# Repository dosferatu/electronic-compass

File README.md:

Electronic-Compass
==================

An electronic compass using an ATMega32U4 microcontroller interfaced to an LSM303DLH accel/magnetomer IC and a Nokia 5110 LCD display.
The sensor is driven through the TWI bus, and the LCD is driven through the SPI bus.

Layout of the PCB is done in Eagle, and the software targets the avr-gcc compiler.

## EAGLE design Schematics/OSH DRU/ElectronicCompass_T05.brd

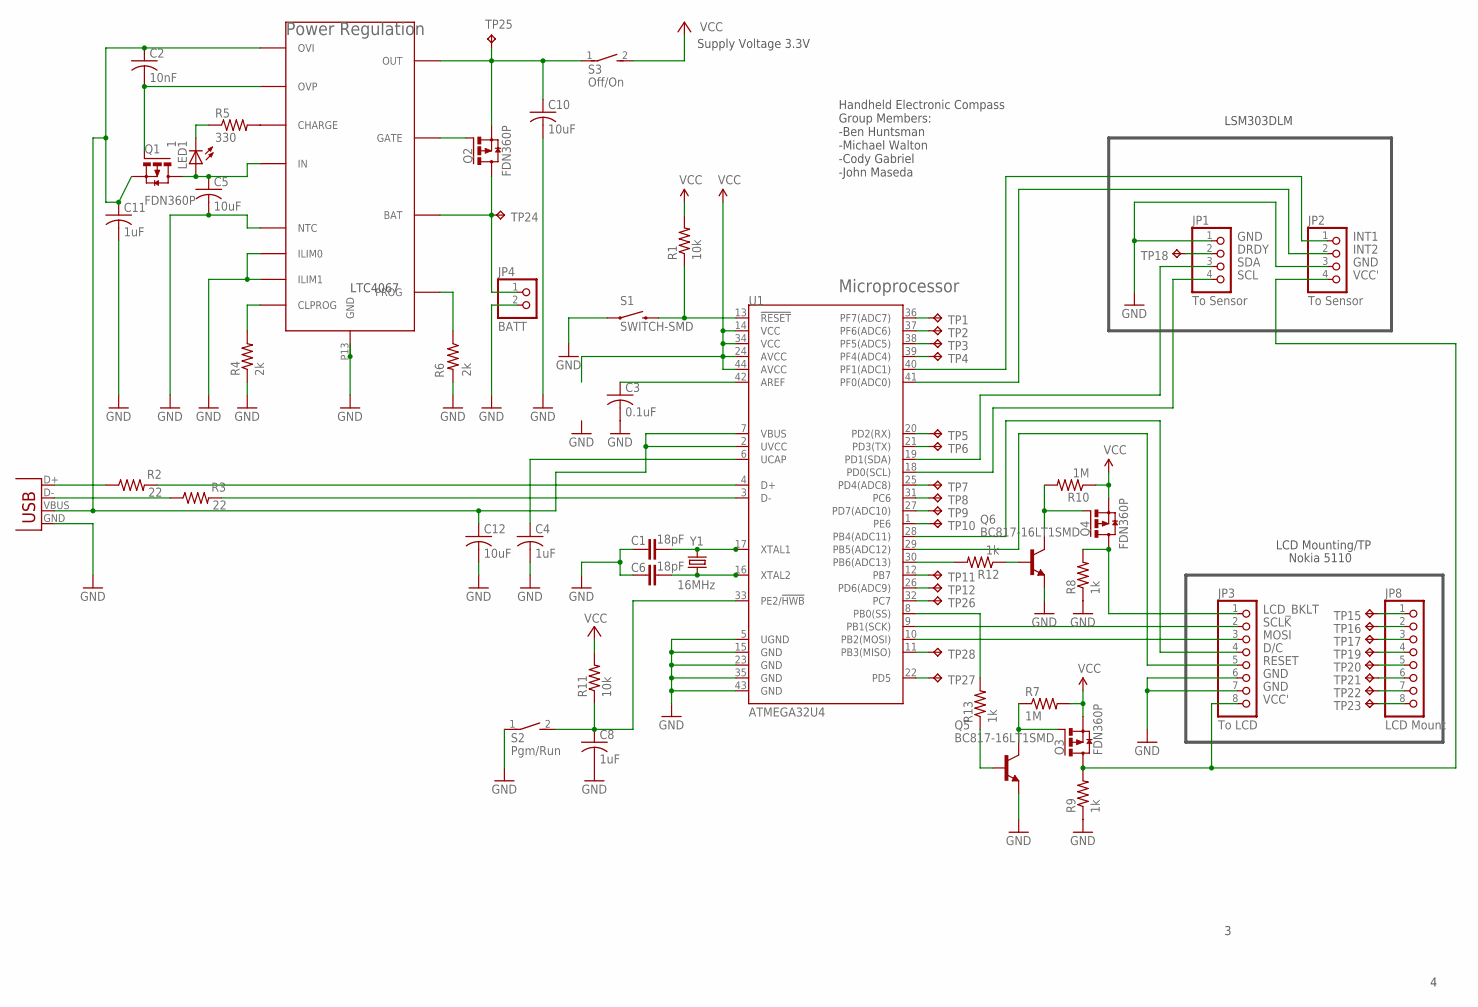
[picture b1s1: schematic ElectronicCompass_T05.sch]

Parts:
C1, C6: 18pF; 0402-CAP
C2: 10nF; C0805
C3: 0.1uF; C0805
C4, C8, C11: 1uF; C0805
C5, C10, C12: 10uF; C0805
JP1, JP2: To Sensor; 1X04
JP3: To LCD; 1X08
JP4: BATT; 1X02
JP8: LCD Mount; 1X08
LED1: 1; CHIPLED_0805
Q1, Q2, Q3, Q4: FDN360P; SUPER-SOT3
Q5, Q6: BC817-16LT1SMD; SOT23-BEC
R1, R11: 10k; M0805
R2, R3: 22; M0805
R4, R6: 2k; M0805
R5: 330; M0805
R7, R10: 1M; M0805
R8, R9, R12, R13: 1k; M0805
S1: SWITCH-SMD; TACTILE_SWITCH_SMD
S2: Pgm/Run; DS-01
S3: Off/On; DS-01
TP1, TP2, TP3, TP4, TP5, TP6, TP7, TP8, TP9, TP10, TP11, TP12, TP15, TP16, TP17, TP18, TP19, TP20, TP21, TP22, TP23, TP24, TP25, TP26, TP27, TP28: TPTP06R; TP06R
U1: ATMEGA32U4; QFN-44-NOPAD
U2: LTC4067; DFN-12
X1: USBSMD; USB-MINIB
Y1: 16MHz; CRYSTAL-SMD-5X3

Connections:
D-: R3.2, U1.3 (D-)
D/C: JP3.4, U1.28 (PB4(ADC11))
DRDY: JP1.2, TP18.TP
GND: C1.1, C3.2, C4.2, C5.2, C6.1, C8.2, C10.2, C11.2, C12.2, JP1.1, JP2.3, JP3.6, JP3.7, JP4.2, Q5.E, Q6.E, R4.1, R6.2, R8.1, R9.1, S1.1, S2.1, U1.5 (UGND), U1.15 (GND), U1.23 (GND), U1.35 (GND), U1.43 (GND), U2.P3 (NTC), U2.P4 (ILIM0), U2.P5 (ILIM1), U2.P13 (GND), X1.GND
INT1: JP2.1, U1.40 (PF1(ADC1))
INT2: JP2.2, U1.41 (PF0(ADC0))
LCD_BKLT: JP3.1, Q4.3 (D), R8.2
MOSI: JP3.3, U1.10 (PB2(MOSI))
unnamed: R6.1, U2.P8 (PROG)
unnamed: TP26.TP, U1.32 (PC7)
unnamed: TP12.TP, U1.26 (PD6(ADC9))
unnamed: R4.2, U2.P1 (CLPROG)
unnamed: JP4.1, Q2.3 (D), TP24.TP, U2.P10 (BAT)
unnamed: C5.1, LED1.A, Q1.3 (D), U2.P12 (IN)
unnamed: R5.2, U2.P2 (CHARGE)
unnamed: LED1.C, R5.1
unnamed: C2.2, Q1.1 (G), U2.P7 (OVP)
unnamed: JP8.8, TP23.TP
unnamed: C8.1, R11.1, S2.2, U1.33 (PE2/!HWB)
unnamed: R3.1, X1.D-
unnamed: R2.1, X1.D+
unnamed: TP1.TP, U1.36 (PF7(ADC7))
unnamed: TP2.TP, U1.37 (PF6(ADC6))
unnamed: R12.2, U1.30 (PB6(ADC13))
unnamed: TP3.TP, U1.38 (PF5(ADC5))
unnamed: TP4.TP, U1.39 (PF4(ADC4))
unnamed: TP5.TP, U1.20 (PD2(RX))
unnamed: TP6.TP, U1.21 (PD3(TX))
unnamed: TP7.TP, U1.25 (PD4(ADC8))
unnamed: TP8.TP, U1.31 (PC6)
unnamed: TP9.TP, U1.27 (PD7(ADC10))
unnamed: TP10.TP, U1.1 (PE6)
unnamed: TP11.TP, U1.12 (PB7)
unnamed: Q4.1 (G), Q6.C, R10.2
unnamed: JP8.7, TP22.TP
unnamed: JP8.6, TP21.TP
unnamed: JP8.5, TP20.TP
unnamed: JP8.4, TP19.TP
unnamed: JP8.3, TP17.TP
unnamed: JP8.2, TP16.TP
unnamed: R2.2, U1.4 (D+)
unnamed: JP8.1, TP15.TP
unnamed: C10.1, Q2.2 (S), S3.1, TP25.TP, U2.P11 (OUT)
unnamed: R13.2, U1.8 (PB0(SS))
unnamed: C3.1, U1.42 (AREF)
unnamed: TP27.TP, U1.22 (PD5)
unnamed: TP28.TP, U1.11 (PB3(MISO))
unnamed: C1.2, U1.17 (XTAL1), Y1.3 (2)
unnamed: C6.2, U1.16 (XTAL2), Y1.1
unnamed: Q6.B, R12.1
unnamed: Q3.1 (G), Q5.C, R7.1
unnamed: Q2.1 (G), U2.P9 (GATE)
unnamed: Q5.B, R13.1
RESET: JP3.5, U1.29 (PB5(ADC12))
RST: R1.1, S1.3 (2), U1.13 (!RESET)
SCL: JP1.4, U1.18 (PD0(SCL))
SCLK: JP3.2, U1.9 (PB1(SCK))
SDA: JP1.3, U1.19 (PD1(SDA))
UCAP: C4.1, U1.6 (UCAP)
VBUS: C2.1, C11.1, C12.1, Q1.2 (S), U1.2 (UVCC), U1.7 (VBUS), U2.P6 (OVI), X1.VBUS
VCC: Q3.2 (S), Q4.2 (S), R1.2, R7.2, R10.1, R11.2, S3.2, U1.14 (VCC), U1.24 (AVCC), U1.34 (VCC), U1.44 (AVCC)
VCC': JP2.4, JP3.8, Q3.3 (D), R9.2

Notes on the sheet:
Microprocessor
Power Regulation
Handheld Electronic Compass Group Members: -Ben Huntsman -Michael Walton -Cody Gabriel -John Maseda
LCD Mounting/TP
LTC4067
LSM303DLM
Nokia 5110
Supply Voltage 3.3V

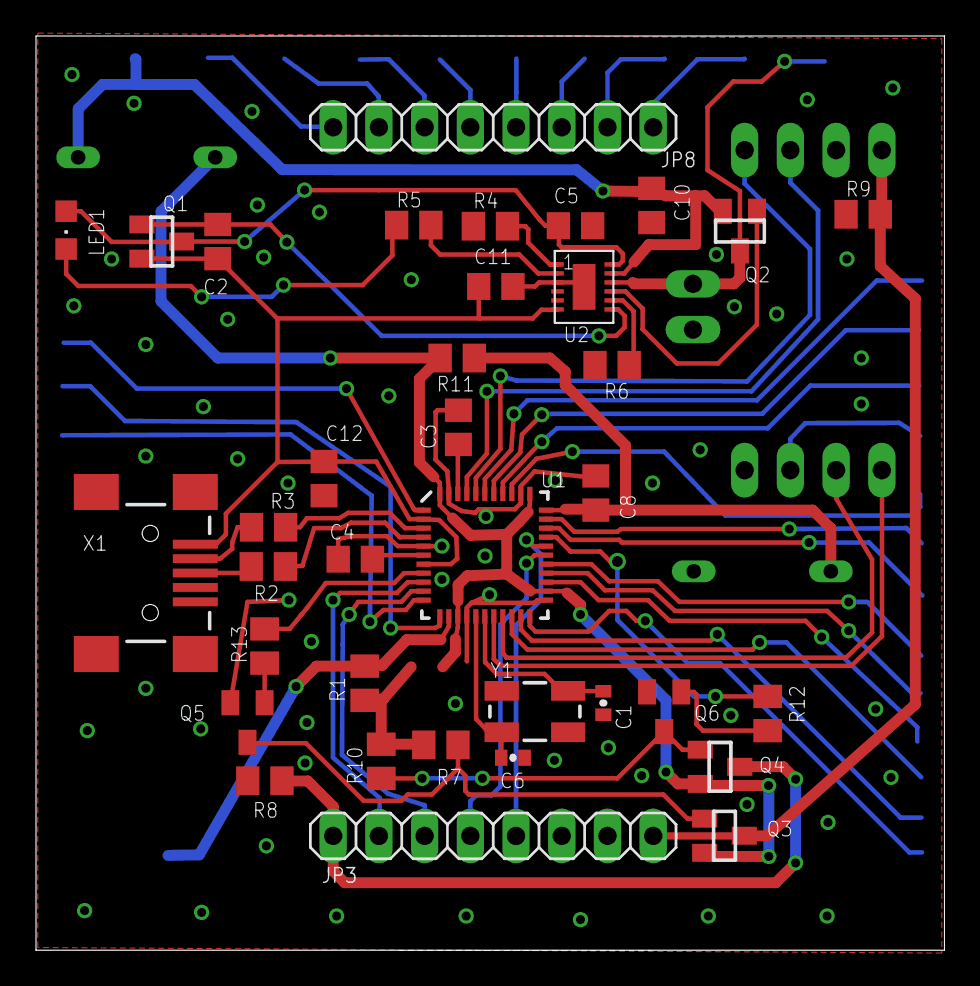
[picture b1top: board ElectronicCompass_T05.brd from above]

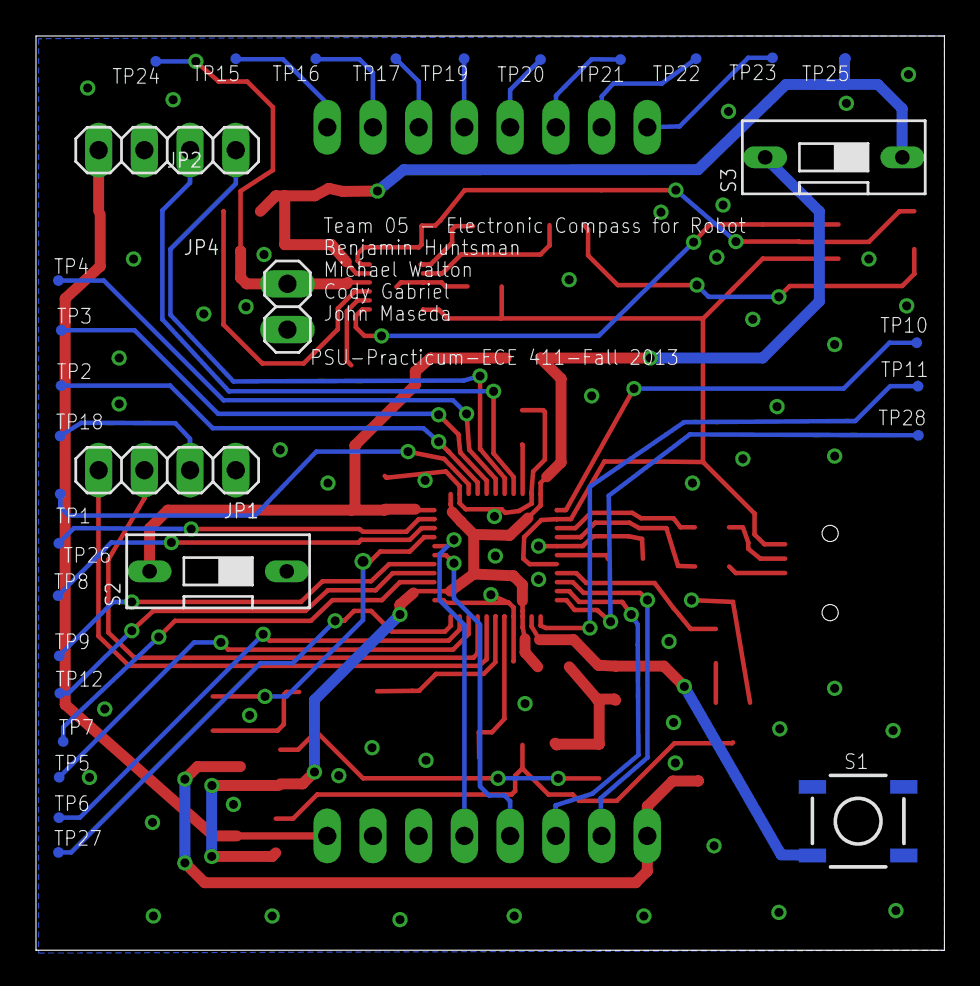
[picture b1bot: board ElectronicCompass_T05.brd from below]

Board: 2 copper layers, 50.5 x 50.8 mm, 68 parts (32 on the bottom side), 62 nets.

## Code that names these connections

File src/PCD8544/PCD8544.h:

#include <avr/io.h>
#include <inttypes.h>

#define LCD_RST                     PORTB |= (1<<PB5)
#define LCD_RST_HI		    PORTB |= (1<<PB5)
#define LCD_RST_LO		    PORTB &= ~(1<<PB5)
#define LCD_DC                      PORTB |= (1<<PB4)
#define LCD_DC_HI		    PORTB |= (1<<PB4)
#define LCD_DC_LO		    PORTB &= ~(1<<PB4)
#define LCD_SDIN                    PORTB |= (1<<PB2)
#define LCD_SCLK		    PORTB |= (1<<PB1)
#define LCD_VDD                     PORTB |= (1<<PB0)
#define LCD_VDD_HI                  PORTB |= ~(1<<PB0)
#define LCD_VDD_LO                  PORTB |= ~(1<<PB0)
#define LCD_BACKLIGHT_HI            PORTB |= (1<<PB6)
#define LCD_BACKLIGHT_LO            PORTB &= ~(1<<PB6)

#define LCD_C                       0
#define LCD_D                       1

#define LCD_WIDTH	            84
#define LCD_HEIGHT	            48

#define UI_LETTERS_X                10
#define UI_LETTERS_Y                2
#define UI_NUMBERS_X                40
#define UI_NUMBERS_Y                2

class PCD8544
{
  public:
    PCD8544();
    ~PCD8544();
    void ClearDisplay();
    void ConvertImage();
    void DisplayHeading(const int);
    void InitPCD8544();
    void SendCommand(const uint8_t);
    void WriteColumn(const uint8_t);

    // For debugging
    void BlinkDisplay(int);

  private:
    void DisplayImage(const uint8_t [][6]);
    void PrintDigit(const int, const int);
    void UpdateLetters(const int);
    void UpdateNumbers(const int);
    void UpdateCompass(const int);
};

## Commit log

2013-10-09 Create gh-pages branch via GitHub
2013-10-22 Initial commit.
2013-10-24 Loaded Requirements doc to repo
2013-10-24 power management for USB charging using 32u4
2013-10-24 Loaded Project Proposal
2013-10-24 Cody's WSR doc
2013-10-24 ATmega32u4 Datasheet
2013-10-24 Loaded ATmega32U4 schematic; To use put it in your EAGLE CAD lbr folder. You won't find it under Atmel but instead under mega32u4 in your library when you search for it.
2013-10-24 Initial Schematic: only includes the ATmega32u4 on it
2013-10-24 Uploaded a bunch of documents that will help with the schematic and/or coding of the ATmega32u4
2013-10-25 More useful docs
2013-10-25 Made changes to the file/folder structure and added some more supporting documentation.
2013-10-26 Did some more moving around and adding some code and libraries from Atmel that might be useful.
2013-10-28 Version 1 Schematic
2013-10-29 Cody's WSR
2013-10-29 Schematic
2013-10-30 Changed some folders: added weekly status report folders for each of us. Also, added some bitmap tests for the screen display.
2013-10-31 Loaded Nokia5110 datasheet
2013-10-31 Changed package types for passives
2013-10-31 Added a PMIC datasheet
2013-11-01 Start integrating Atmel supplied TWI driver in to project.
2013-11-01 Modified main to include an interrupt enable.
2013-11-01 loaded some more stuff
2013-11-03 Schematic w/PMIC
2013-11-04 Schematic 1st draft
2013-11-04 Symbol and footprint for LTC4067 PMIC
2013-11-04 weekly progress report
2013-11-04 updated schematic - added some traces
2013-11-04 Changed unused GPIO's to test points
2013-11-04 Schematic - rotated some GND and Vcc to dwn and up
2013-11-04 Board Layout- Began (very rough) laying parts
2013-11-05 WSR for week of 10/28/13
2013-11-05 Added my weekly status reports from local drive
2013-11-05 Added weekly status reports from local drive
2013-11-05 needed WSRs to be one per week
2013-11-05 fixed the WPRs
2013-11-06 Fixed header pins, some aesthetics
2013-11-07 PMOS switch modeled in LTSpice
2013-11-07 Made it prettier...
2013-11-07 Added ON/OFF switch
2013-11-07 Nothing on the doc, just an empty project
2013-11-09 The schematic has been finalized!
2013-11-10 Started filling it out
2013-11-10 Updated schematic/board layout check list. Submitted WPR for week of 11/5/13.
2013-11-10 Last minute changes to schematic before the layout begins
2013-11-10 Better schedule
2013-11-10 More Schedule stuff
2013-11-10 moved schedule to appropriate folder
2013-11-10 asdfjkl;
2013-11-10 asdf
2013-11-10 added the changes as a new file so you could take a look at them.
2013-11-11 Board layout changes
2013-11-11 Initial code for the compass with LSM303 interface.
2013-11-11 Initial compass software with working LSM303 library.
2013-11-11 Restructured the src folder, and included an open source glcd library for the Nokia 5110 LCD.
2013-11-11 Trying to fix the glcd directory
2013-11-11 Fixed the glcd library included in the project.
2013-11-11 Fixed the make file to clean properly and to define avr delays for glcd
2013-11-11 Changed the project description to be a little more meaningful.
2013-11-11 board layout continued
2013-11-11 made some updates to the layout checklist
2013-11-11 New transistors
2013-11-11 loaded a hex file with the image for the lcd
2013-11-11 xtal added
2013-11-11 gpio change push
2013-11-12 WBS and Schedule updated
2013-11-12 board layout complete
2013-11-12 WPR 11-05-2013
2013-11-12 Cody
2013-11-12 push xtal move
2013-11-12 Grounded current limiting programming pins on PMIC
2013-11-14 Made some changes to the schematic recommended by Andrew. It is not finished yet but there are some major changes that need to be done before we turn this thing in.
2013-11-15 Made some more updates to the schematic according to what Andrew suggested. Still need to put in the new batter header and then fix the board layout.
2013-11-15 WBS update
2013-11-15 Document that was submitted to Faust
2013-11-15 Made some updates to the schem and board. Still a lot of issues with the board layout that need to be worked out.
2013-11-16 Fixed transistor switches
2013-11-16 LTSpice switch simulation
2013-11-16 sch changes
2013-11-16 New components
2013-11-16 Working LSM393 interface without proper calibration values.
2013-11-16 sch update
2013-11-16 no changes
2013-11-17 sch and layout changes
2013-11-17 layout done
2013-11-17 System Model
2013-11-17 layout update
2013-11-17 staples
2013-11-17 ready
2013-11-17 More symbols
2013-11-17 Isolated ground plane
2013-11-18 Level 0 and 1 diagrams and descriptions complete
2013-11-18 Added weekly status report
2013-11-18 Small change, restarting computer
2013-11-18 Loads some updates to the LCD display and images
2013-11-18 Fix Git Sync Issue
2013-11-18 Layout stuff and Modeling stuff
2013-11-18 asdkjfsd
2013-11-18 fixing git
2013-11-18 Added files back
2013-11-18 Adding board layout files
2013-11-19 Pin change on LTC4067
2013-11-19 Updated System Model
2013-11-19 Simulated change to switch
2013-11-19 updated changes to board layout
2013-11-19 Fixed PMIC pins and GPIO switches
2013-11-19 Loaded up WPR and other stuff
2013-11-19 loaded some LCD interface changes
2013-11-19 Added Physical UML view
2013-11-19 WPR - Cody
2013-11-19 BOM uploaded
2013-11-19 Refactoring code tree
2013-11-19 Included image parts header for PCD8544 library
2013-11-19 s-screen layout update
2013-11-19 Added the class diagram and stuff
2013-11-20 BOM checklist
2013-11-20 HW ready
2013-11-21 some changes to format of the LCD files
2013-11-21 restructured folders and got rid a duplicate folder
2013-11-23 Made some changes to the LCD library and added the content of the m32io.h file so that we can see what all the registers are set as for our MU.
2013-11-24 Started display interface.
2013-11-25 weekly progress report update
2013-11-25 Created PCD8544 display controller initialization function
2013-11-25 Nothing special done, just using the file
2013-11-25 This is a rough draft of the test plan
2013-11-25 loaded WPR
2013-11-26 Fixed image arrays= bugs by explicitly loading from flash.
2013-11-26 Initial work on temporary string print function for LCD.
2013-11-26 Fixed display initialization
2013-11-27 Test case for PMIC
2013-11-27 Work done on UI, added in test plan document.
2013-11-27 Added intro to test plan
2013-11-27 Work on Test Plan
2013-11-27 made changes to test plan
2013-11-27 Added test case to test plan
2013-11-27 Bug fix on test plan
2013-11-28 More work on UI
2013-11-29 Implemented drawing letters for heading in UI
2013-11-29 Started work on drawing numbers for the UI
2013-11-30 Finished UI.
2013-12-03 Created solder mask gerber file.
2013-12-05 updated BOM
2013-12-05 outline for presentation given by Faust
2013-12-06 Added stuff to presentation outline
2013-12-06 layout page
2013-12-08 Two-weeks worth of WSR's ><
2013-12-08 Added a few things to the outline
2013-12-09 Started filling out Pwr. Pt.
2013-12-10 Added more to Pwr. Pt
2013-12-10 Small Changes to pwr pt
2013-12-12 Added more to PPT
2013-12-12 Updated Design model and PPT
2013-12-12 Minor editing of proposal
2013-12-13 Minor changes to PPT
2013-12-13 Work on implementing finished product sw release
2013-12-13 add some avr files for use to see defines.
2013-12-13 Working compass without calibration.
2013-12-13 Working compass without calibration
2013-12-13 Updated makefile to allow specifying avrdude or dfu-programmer.
2013-12-13 updated presentation
2013-12-13 added finances document
2014-11-09 Removed capacitor
